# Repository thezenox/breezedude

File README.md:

# BreezeDude
### An Open source low power FANET wind sensor.

Map of almost all wind stations: https://breezedude.de/

For more info and docs see the [Wiki](https://github.com/thezenox/breezedude/wiki)

----
<p align="center">
  <
  
   <br>
  <br>
</p>

A low cost FANET wind station using Ecowitt WS80/WS85 ultrasonic or DAVIS 6410 analog sensor.     
USB MSC Settings file and Drag&Drop Firmware upgrade. 

- wind sensor: Ecowitt WS80/WS85 or analog with reed/potentiometer (e.g. DAVIS 6410)
- pressure sensor: HP303B, BMP280, BMP3xx or SPL06-001
- LoRa module: RFM95W (SX1276), G-NiceRF SX1262, LLCC68
- antenna connector: SMA
- microcontroller: SAMD21
- connectivity: USB-C, I2C, 2x UART
- battery: 1S Li-Ion 16340 750mAh (or 1-3x 18650 external)
- solar: 5V
- PCB Size: 53x22mm

Currently using a 60x60 5V solar panel.     
Avg. power consumption at 40s send interval @3.7V battery: 1.2mA with analog sensor, 2.22mA with WS80
 
Based on SMAD21 using [adafruits samd core](https://github.com/adafruit/ArduinoCore-samd) and itsybitsy M0 variant definitions and [bootloader](https://github.com/adafruit/uf2-samdx1).     

#### Related projects and inspiration:
* https://github.com/gereic/GXAirCom
* https://github.com/jgromes/RadioLib
* https://github.com/3s1d/fanet-stm32

If you like this project

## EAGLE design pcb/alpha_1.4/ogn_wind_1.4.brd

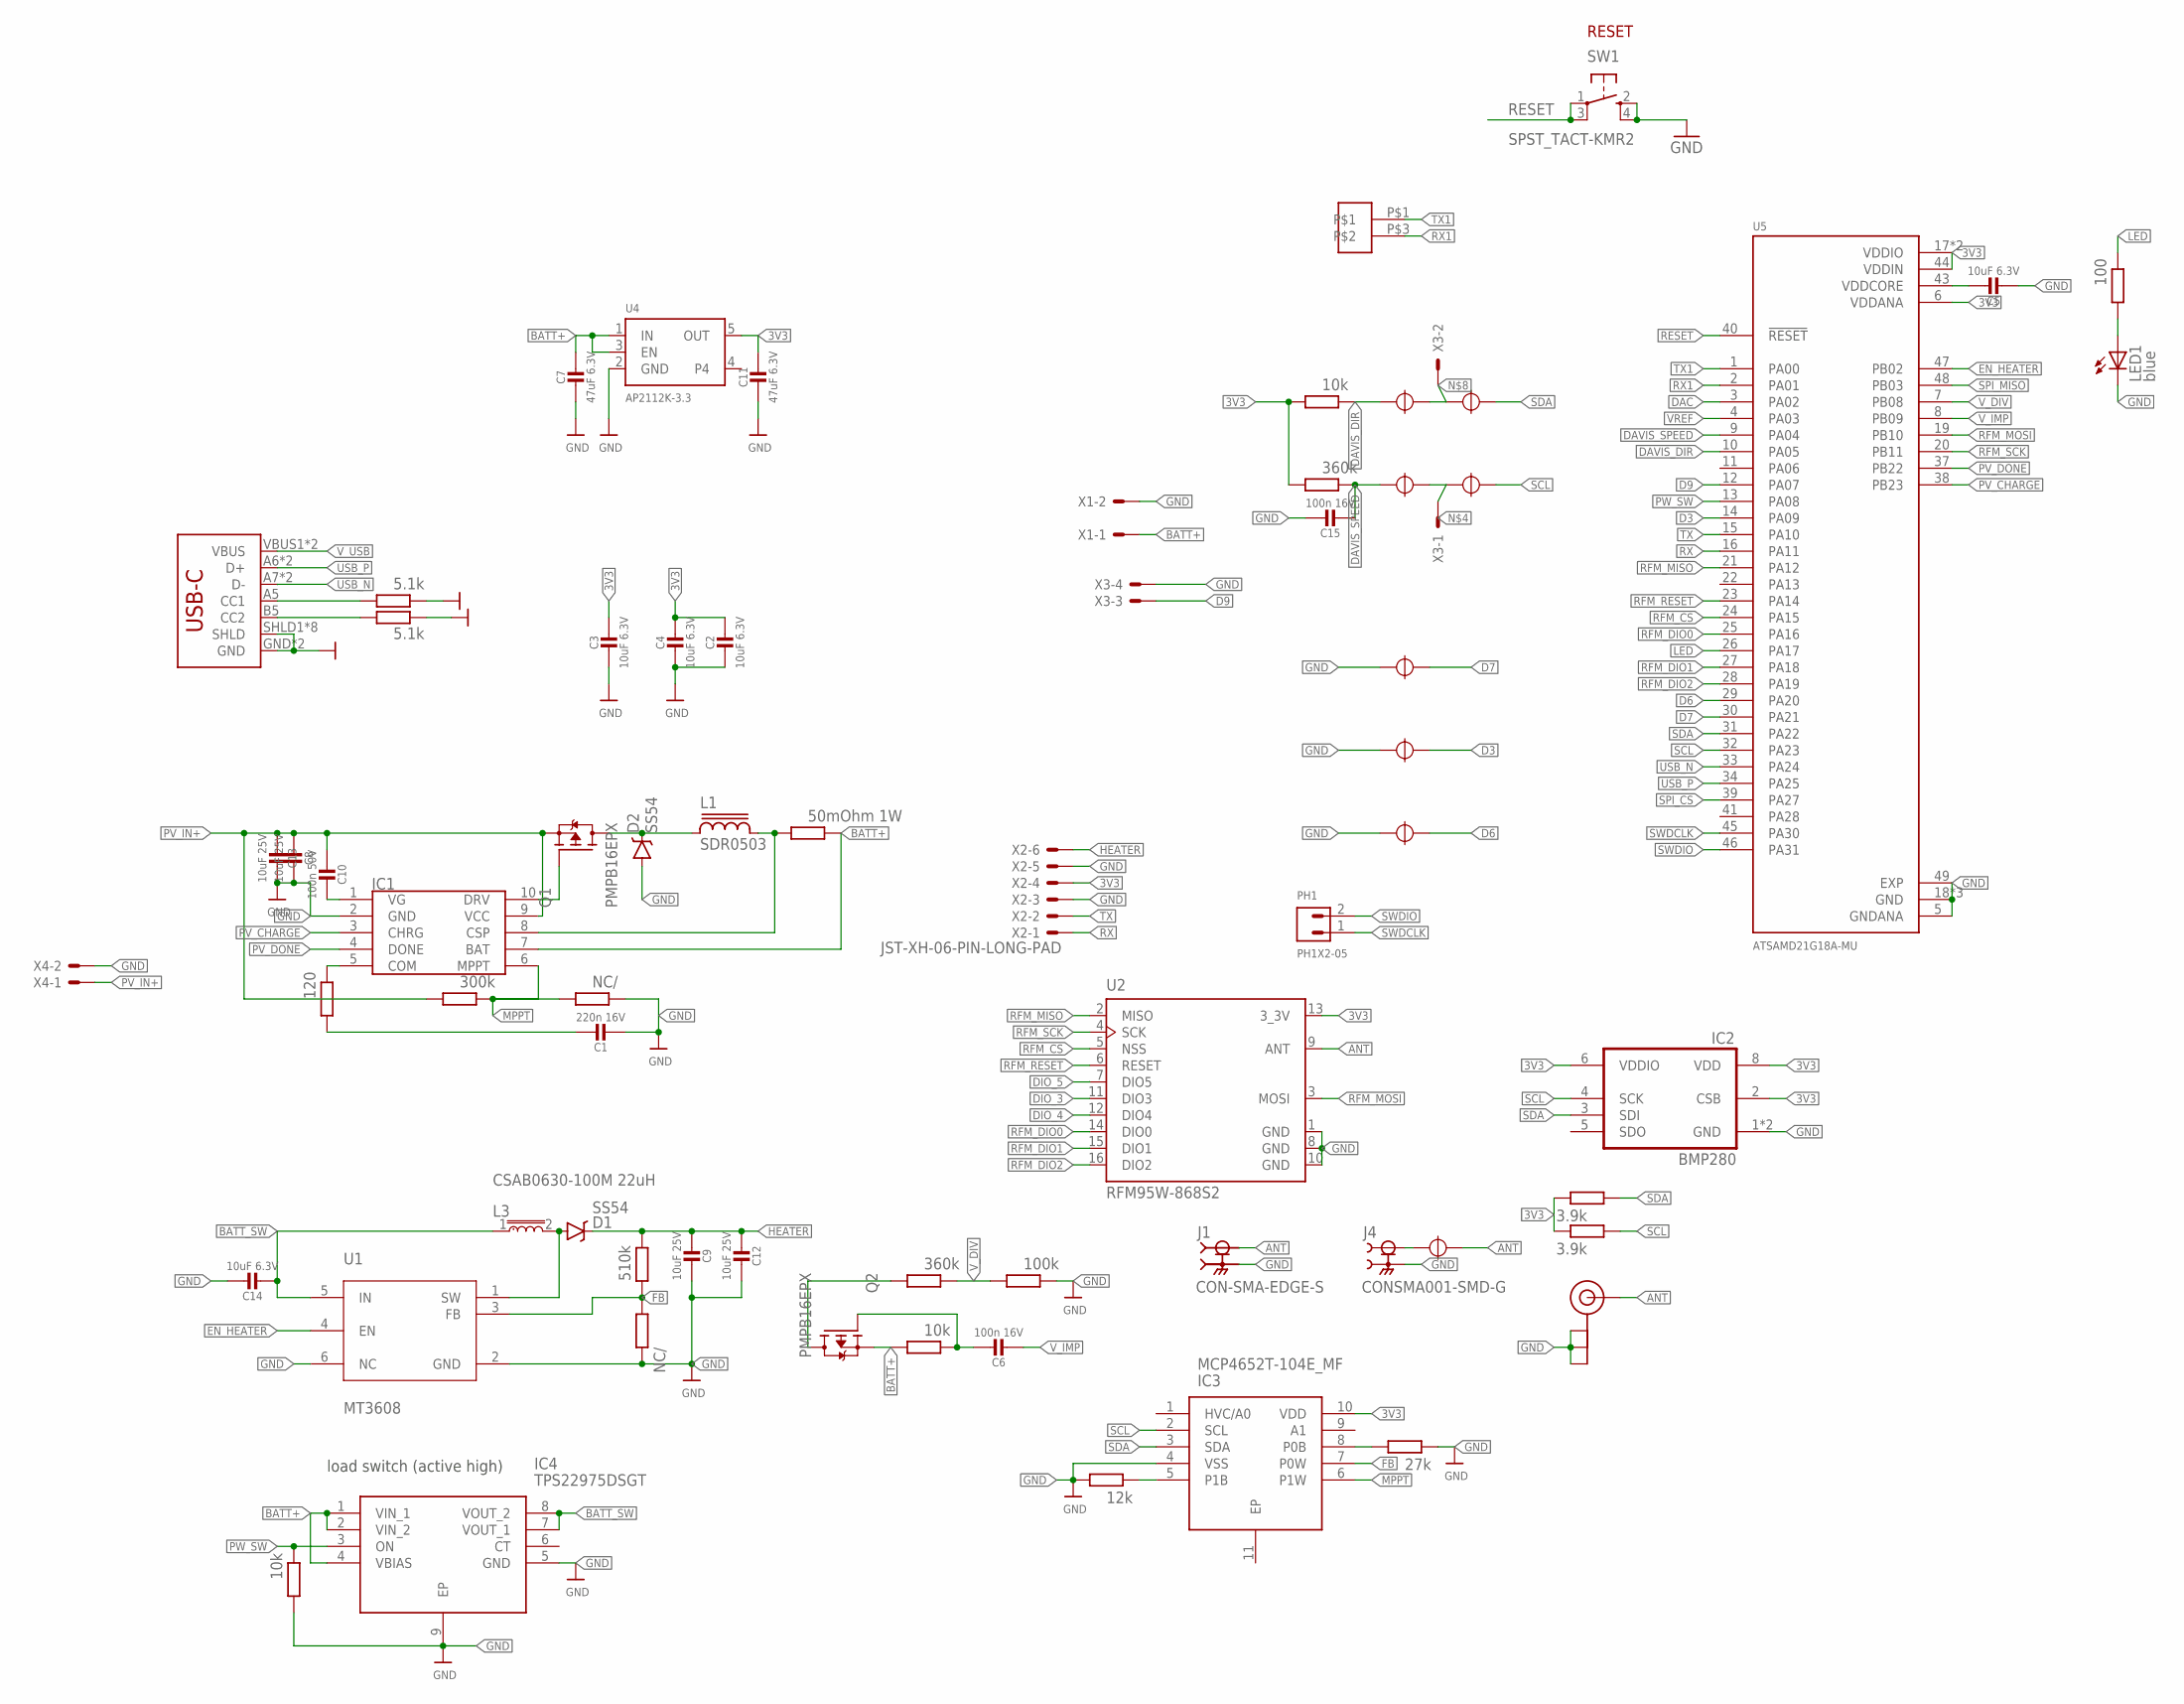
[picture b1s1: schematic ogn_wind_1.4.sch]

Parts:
ANT_UFL: U.FL
C1: 220n 16V; _0402MP
C2, C3, C4, C5, C14: 10uF 6.3V; _0402MP
C6, C15: 100n 16V; _0402MP
C7, C11: 47uF 6.3V; 0805-NO
C8, C9, C12, C13: 10uF 25V; _0603MP
C10: 100n 50V; _0603MP
D1, D2: SS54; DO-214AC
IC1: CN3791; SSOP10
IC2: BMP280
IC3: MCP4652T-104E_MF; SON50P300X300X100-11N
IC4: TPS22975DSGT; SON50P200X200X80-9N; JLCPCB C524777
J1: CON-SMA-EDGE-S; RFSOLUTIONS_CON-SMA-EDGE-S
J2: USB_C16PIN; USB-C-16P
J4: CONSMA001-SMD-G; LINX_CONSMA001-SMD-G
L1: SDR0503
L3: CSAB0630-100M 22uH; INDC6060X300
LED1: blue; CHIPLED_0603
PH1: PH1X2-05; PH005-1-2
Q1, Q2: PMPB16EPX; TRANS_PMPB16EPX; JLCPCB C919545
SW1: SPST_TACT-KMR2; KMR2
U1: MT3608; SOT95P280X145-6N
U2: RFM95W-868S2; XCVR_RFM95W-868S2
U4: AP2112K-3.3; SOT23-5
U5: ATSAMD21G18A-MU; QFN50P700X700X90-49N
U$1, U$2, U$3, U$4, U$7, U$10, U$11, U$22: SJ
U$13: SMDPAD2
USBCR, USBCR1: 5.1k; 0402RF
USBCR2, USBCR12: 360k; 0402RF
USBCR3: 100k; 0402RF
USBCR4, USBCR5, USBCR11: 10k; 0402RF
USBCR6: 300k; 0402RF
USBCR7, USBCR10: NC/; 0402RF
USBCR8: 120; 0402RF
USBCR9: 510k; 0402RF
USBCR13: 100; 0402RF
USBCR14, USBCR15: 3.9k; 0402RF
USBCR17: 27k; 0402RF
USBCR18: 12k; 0402RF
USBCR19: 50mOhm 1W; R1206
X1, X4: JST-XH-02-PIN-LONG-PAD; JST-XH-02-PACKAGE-LONG-PAD
X2: JST-XH-06-PIN-LONG-PAD; JST-XH-06-PACKAGE-LONG-PAD
X3: JST-XH-04-PIN-LONG-PAD; JST-XH-04-PACKAGE-LONG-PAD

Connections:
3V3: C2.1, C3.1, C4.1, C11.1, IC2.2 (CSB), IC2.6 (VDDIO), IC2.8 (VDD), IC3.10 (VDD), U2.13 (3_3V), U4.5 (OUT), U5.6 (VDDANA), U5.17 (VDDIO), U5.36 (VDDIO), U5.44 (VDDIN), USBCR11.1, USBCR12.1, USBCR14.2, USBCR15.2, X2.4
ANT: ANT_UFL.P$3 (SIGNAL), J1.1, U2.9 (ANT), U$22.P$2
BATT+: C7.1, IC1.7 (BAT), IC4.1 (VIN_1), IC4.2 (VIN_2), IC4.4 (VBIAS), Q2.4 (S), Q2.8 (S), U4.1 (IN), U4.3 (EN), USBCR4.1, USBCR19.2, X1.1
BATT_SW: C14.2, IC4.7 (VOUT_1), IC4.8 (VOUT_2), L3.1, U1.5 (IN)
D3: U5.14 (PA09), U$10.P$2
D6: U5.29 (PA20), U$11.P$2
D7: U5.30 (PA21), U$7.P$2
D9: U5.12 (PA07), X3.3
DAC: U5.3 (PA02)
DAVIS_DIR: U5.10 (PA05), U$3.P$1, USBCR11.2
DAVIS_SPEED: C15.2, U5.9 (PA04), U$1.P$1, USBCR12.2
DIO_3: U2.11 (DIO3)
DIO_4: U2.12 (DIO4)
DIO_5: U2.7 (DIO5)
EN_HEATER: U1.4 (EN), U5.47 (PB02)
FB: IC3.7 (P0W), U1.3 (FB), USBCR9.1, USBCR10.1
FB_R: IC3.8 (P0B), USBCR17.1
GND: ANT_UFL.P$1 (GND), ANT_UFL.P$2 (GND), ANT_UFL.P$4 (GND), C1.2, C2.2, C3.2, C4.2, C5.2, C7.2, C8.2, C9.1, C11.2, C12.1, C13.2, C14.1, C15.1, D2.A, IC1.2 (GND), IC2.1 (GND), IC2.7 (GND), IC3.4 (VSS), IC4.5 (GND), IC4.9 (EP), J1.G1 (2), J1.G2 (2), J1.G3 (2), J1.G4 (2), J2.GND, J2.GND2 (GND), J2.SHLD1 (SHLD), J2.SHLD2 (SHLD), J2.SHLD3 (SHLD), J2.SHLD4 (SHLD), J2.SHLD5 (SHLD), J2.SHLD6 (SHLD), J2.SHLD7 (SHLD), J2.SHLD8 (SHLD), J4.S1 (2), J4.S2 (2), LED1.C, SW1.2 (S), SW1.4 (S1), U1.2 (GND), U1.6 (NC), U2.1 (GND), U2.8 (GND), U2.10 (GND), U4.2 (GND), U5.5 (GNDANA), U5.18 (GND), U5.35 (GND), U5.42 (GND), U5.49 (EXP), U$7.P$1, U$10.P$1, U$11.P$1, USBCR.2, USBCR1.2, USBCR3.2, USBCR5.1, USBCR7.2, USBCR10.2, USBCR17.2, USBCR18.1, X1.2, X2.3, X2.5, X3.4, X4.2
HEATER: C9.2, C12.2, D1.C, USBCR9.2, X2.6
LED: U5.26 (PA17), USBCR13.2
MPPT: IC1.6 (MPPT), IC3.6 (P1W), USBCR6.2, USBCR7.1
MPPT_R: IC3.5 (P1B), USBCR18.2
unnamed: IC1.10 (DRV), Q1.3 (G)
unnamed: D2.C, L1.1, Q1.1 (D), Q1.2 (D), Q1.5 (D), Q1.6 (D), Q1.7 (D)
unnamed: IC1.8 (CSP), L1.2, USBCR19.1
unnamed: U$1.P$2, U$2.P$1, X3.1
unnamed: LED1.A, USBCR13.1
unnamed: Q2.1 (D), Q2.2 (D), Q2.5 (D), Q2.6 (D), Q2.7 (D), USBCR2.1
unnamed: C10.1, IC1.1 (VG)
unnamed: U$3.P$2, U$4.P$1, X3.2
unnamed: J4.1, U$22.P$1
unnamed: C1.1, USBCR8.1
unnamed: IC1.5 (COM), USBCR8.2
unnamed: C6.1, Q2.3 (G), USBCR4.2
unnamed: J2.A5 (CC1), USBCR.1
unnamed: J2.B5 (CC2), USBCR1.1
PV_CHARGE: IC1.3 (CHRG), U5.38 (PB23)
PV_DONE: IC1.4 (DONE), U5.37 (PB22)
PV_IN+: C8.1, C10.2, C13.1, IC1.9 (VCC), Q1.4 (S), Q1.8 (S), USBCR6.1, X4.1
PW_SW: IC4.3 (ON), U5.13 (PA08), USBCR5.2
RESET: SW1.1, SW1.3 (P1), U5.40 (!RESET)
RFM_CS: U2.5 (NSS), U5.24 (PA15)
RFM_DIO0: U2.14 (DIO0), U5.25 (PA16)
RFM_DIO1: U2.15 (DIO1), U5.27 (PA18)
RFM_DIO2: U2.16 (DIO2), U5.28 (PA19)
RFM_MISO: U2.2 (MISO), U5.21 (PA12)
RFM_MOSI: U2.3 (MOSI), U5.19 (PB10)
RFM_RESET: U2.6 (RESET), U5.23 (PA14)
RFM_SCK: U2.4 (SCK), U5.20 (PB11)
RX: U5.16 (PA11), X2.1
RX1: U5.2 (PA01), U$13.P$3
SCL: IC2.4 (SCK), IC3.2 (SCL), U5.32 (PA23), U$2.P$2, USBCR15.1
SDA: IC2.3 (SDI), IC3.3 (SDA), U5.31 (PA22), U$4.P$2, USBCR14.1
SPI_CS: U5.39 (PA27)
SPI_MISO: U5.48 (PB03)
SW: D1.A, L3.2, U1.1 (SW)
SWDCLK: PH1.1, U5.45 (PA30)
SWDIO: PH1.2, U5.46 (PA31)
TX: U5.15 (PA10), X2.2
TX1: U5.1 (PA00), U$13.P$1
USB_N: J2.A7 (D-), J2.B7 (D-), U5.33 (PA24)
USB_P: J2.A6 (D+), J2.B6 (D+), U5.34 (PA25)
VDDCORE: C5.1, U5.43 (VDDCORE)
VREF: U5.4 (PA03)
V_DIV: U5.7 (PB08), USBCR2.2, USBCR3.1
V_IMP: C6.2, U5.8 (PB09)
V_USB: J2.VBUS1 (VBUS), J2.VBUS2 (VBUS)

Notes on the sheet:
RESET
load switch (active high)

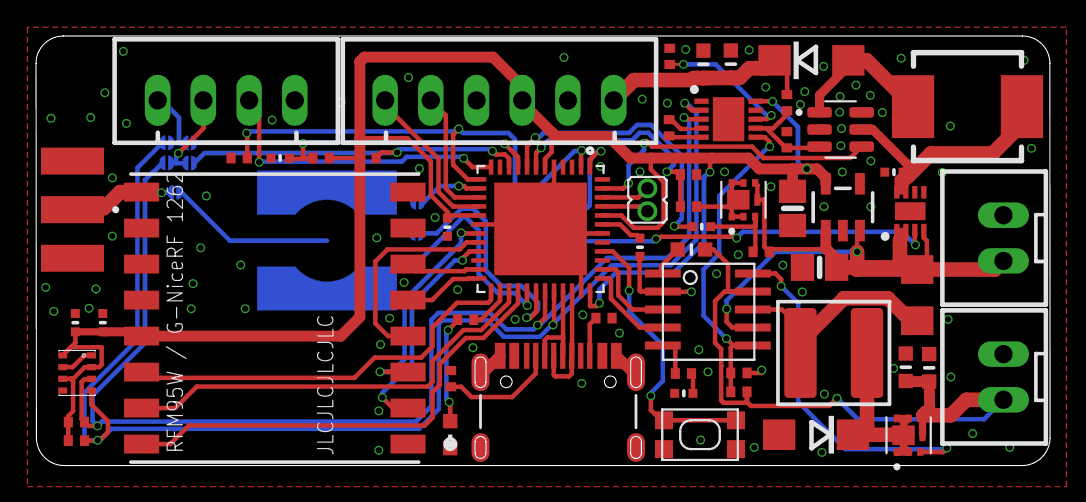
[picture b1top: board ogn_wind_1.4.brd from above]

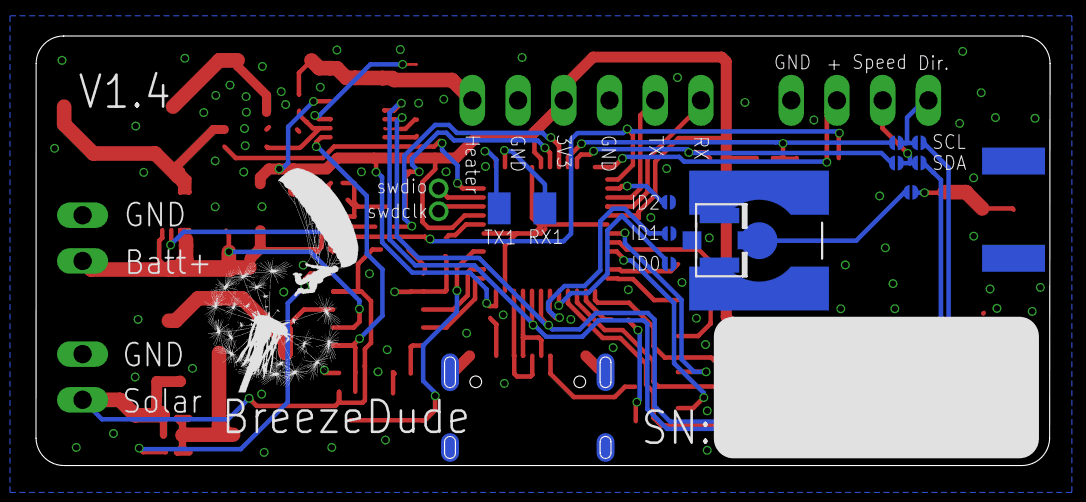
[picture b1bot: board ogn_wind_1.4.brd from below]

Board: 2 copper layers, 56.3 x 23.9 mm, 68 parts (11 on the bottom side), 60 nets.

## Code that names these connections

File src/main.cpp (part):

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#include "display.h"
#include "hist.h"

 #define HAS_HEATER // support for Heater (HW V1.x)

// Todo list:
// * Read bootloader version
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// 1 { PORTA, 10, PIO_SERCOM, (PIN_ATTR_DIGITAL), No_ADC_Channel, NOT_ON_PWM, NOT_ON_TIMER, EXTERNAL_INT_10 }, // TX: SERCOM0/PAD[2]

// SERCOM 4 - SPI RFM95W LoRa
#define PIN_LORA_MISO MISO  // 28 PA12  - SERCOM2/PAD[0] | alt SERCOM4/PAD[0]
#define PIN_LORA_MOSI MOSI  // 29 PB10  -                | alt SERCOM4/PAD[2]
#define PIN_LORA_SCK SCK    // 30 PB11  -                | alt SERCOM4/PAD[3]

#define PIN_LORA_CS 5    // PA15 - SERCOM2/PAD[3] | alt SERCOM4/PAD[3]
#define PIN_LORA_RESET 2 // PA14 - SERCOM2/PAD[2] | alt SERCOM4/PAD[2]
#define PIN_LORA_DIO0 11 // PA16 - SERCOM1/PAD[0] | alt SERCOM3/PAD[0]
#define PIN_LORA_DIO1 10 // PA18 - SERCOM1/PAD[2] | alt SERCOM3/PAD[2]
#define PIN_LORA_DIO2 12 // PA19 - SERCOM1/PAD[3] | alt SERCOM3/PAD[3]
#define PIN_LORA_DIO3 3  // PA09 - SERCOM0/PAD[1], ADC
#define PIN_PV_CHARGE 38// PB23
#define PIN_PV_DONE 37 // PB22
#define PIN_PS_WS 36 // PB03 PIO_SERCOM_ALT, PIN_ATTR_NONE, No_ADC_Channel, NOT_ON_PWM, NOT_ON_TIMER, EXTERNAL_INT_NONE },  // SPI Flash MISO on ItsyBitsy M0, Power switch control for WSXX Sensor. HW >= 2.2

#define PIN_SERCOM1_TX 40 // PA00 SERCOM1 PAD0
#define PIN_SERCOM1_RX 10 // PA01 SERCOM1 PAD1

// Pins with solder jumpers 
#define PIN_ID0 6 // PA20 - SERCOM5/PAD[2]
#define PIN_ID1 7 // PA21 - SERCOM5/PAD[3]


// Serial2 for Degugging on HW > 1.3
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
#ifdef HAS_HEATER
  #define HEATER_MAX_V 9.20 // Maximum setpoint voltage, thermal limit by inductor (~1,8A conntiniuos, actual voltage ~8V)
  #define PIN_EN_DCDC 19 // A5 19 PB02
  #define PIN_EN_HEATER 4 //D4/A8 PA08
#endif


#define PIN_DAVIS_SPEED 17 // A3 17 PA04
#define PIN_DAVIS_DIR 18 // A4 18 PA05
#define PIN_DAVIS_POWER 9 // 9 PA07 - power for direction potentiometer. Turn off if not used to save power

// SERCOM 3 - I²C Barometer / Digipot
#define PIN_SDA 26 // PA22
#define PIN_SCL 27 // PA23

// I2C Barometer
BMP280 bmp280; // Bosch BMP280
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// Yellow - Pot supply voltage

// SERCOM 0 - uart serial Sensor/ GPS / Debug
#define PIN_RX 0 // A6 PA11
#define PIN_TX 1 // A7 PA10

#define PIN_STATUSLED 13 // PA17 // blue, 1.2mA @ 2.77V = 470Ohm
#define PIN_ERRORLED 4 //D4/A8 PA08 // red 2.9mA @ 2.16V = 390Ohm
#define PIN_V_READ_TRIGGER A2 // D16 PB09
#define PIN_V_READ A1 // D15 PB08 - { PORTB,  8, PIO_ANALOG, (PIN_ATTR_PWM|PIN_ATTR_TIMER), ADC_Channel2, PWM4_CH0, TC4_CH0, EXTERNAL_INT_8 }, // ADC/AIN[2]

#define VERSIONFILE (char*) "version.txt"
#define SETTINGSFILE (char*) "settings.txt"
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
#define MCP4652_I2C_ADDR	0x2F
#define WRITE_WIPER_DCDC	(0b0000<<4) // Wiper 0 = DCDC
#define WRITE_WIPER_MPPT	(0b0001<<4) // Wiper 1 = MPPT
#define WRITE_TCON	(0b0100<<4)
#define CMD_WRITE	(0b00<<2)

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
// read status pins of solar charger
void get_solar_charger_state(){
  pinMode(PIN_PV_CHARGE, INPUT_PULLUP);
  pinMode(PIN_PV_DONE, INPUT_PULLUP);
  pv_done = !digitalRead(PIN_PV_DONE);
  pv_charging = !digitalRead(PIN_PV_CHARGE);
  pinDisable(PIN_PV_CHARGE);
  pinDisable(PIN_PV_DONE);
}

// Trigger ADC and calc battery value in percent and volts
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int read_wind_dir(){
  int val = 0;
  analogReference(AR_DEFAULT); //3.3V refernece
  pinMode(PIN_DAVIS_DIR, INPUT);
  pinMode(PIN_DAVIS_POWER,OUTPUT);
  digitalWrite(PIN_DAVIS_POWER,1);

int d = analogRead(PIN_DAVIS_DIR);


if(is_davis6410){
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 // ... other analog sensors
digitalWrite(PIN_DAVIS_POWER,0);
pinDisable(PIN_DAVIS_POWER);
pinDisable(PIN_DAVIS_DIR);
return val;
}

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    if(!current_output_v){ // is currently off
      current_output_v = 3; // start at 3V (non switching)
      mcp4652_write(WRITE_WIPER_DCDC, calc_mt3608(current_output_v)); // to avoid 1,1A short circuit detection set to half voltage at load switch enable
      pinMode(PIN_EN_HEATER,OUTPUT);
      pinMode(PIN_EN_DCDC,OUTPUT);
      digitalWrite(PIN_EN_HEATER,1);
      delay(5);
      digitalWrite(PIN_EN_DCDC,1);
      h_switch_on_time = time();
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    if(h_switch_on_time){
      h_switch_on_time=0;
      current_output_v=0;
      digitalWrite(PIN_EN_HEATER,0);
      digitalWrite(PIN_EN_DCDC,0);
      pinDisable(PIN_EN_HEATER);
      pinDisable(PIN_EN_DCDC);
      log_i("Heater turned off: ", time());
    }
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    wdt_disable();
  }

// Using TC4 for hardware pulsecounting on Falling edge on pin PA04 (D17). No interrupts needed.
  if(!undervoltage && is_davis6410){ // pulse counting anemometer
    actual_sleep = rtc_sleep_cfg(time_to_sleep);
    setup_pulse_counter(); // need to setup GCLK6 before
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
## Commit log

2024-02-26 init
2024-03-03 include altitude in FANET name broadcast
2024-03-14 fix name
2024-04-11 fix whitespace in name, add support for SPL06 barometer
2024-04-12 continuous sampling of ws80 while in deepsleep. added short term wind history for averaging and better gust tracking
2024-06-01 added images
2024-06-01 add pictures and basic infos
2024-06-01 add flashing instruction for factory new samd21
2024-12-27 mini V2.0
2025-01-03 v2.1. fixed p-fet, added vollgo cc68, vertical SMA
2025-01-28 0.4. moved to radiolib, added some debugging features, more baro supported, added I2C display
2025-02-08 improved WS85/85 data reading + autodetection
2025-02-14 add mini v2 picture
2025-05-04 mini V2.2
2025-05-04 LICENSE.txt
2025-05-06 add support for HP203B pressure sensor
2025-06-06 Update README.md
    add link to wiki
2025-06-12 add bootloader & firmware binaries

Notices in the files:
parts and their libraries:
microbuilder: This work is placed in the public domain, and may be freely used for commercial and non-commercial work with the following conditions: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
SparkFun-Connectors: Licensing: Creative Commons ShareAlike 4.0 International - https://creativecommons.org/licenses/by-sa/4.0
